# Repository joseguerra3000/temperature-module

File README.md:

Temperature Module
==================
Temperature module of small dimensions (approximately 45x25mm), compatible with arduino and digilent cerebot.
Useful for data acquisition systems based on microcontrollers (arduino, pic, etc.) and as a thermoresistor calibrator.
Able to use three temperature sensors at the same time:
  - LM35
  - AD22103
  - thermoresistor

How to use it
-------------
It only needs to be powered with +5V and +3.3V to measure temperatures greater thad 0°C with LM35 and AD22103 sensors. 
Optionally it can also be supplied with -5V to measure temperatures below 0°C with the LM35 sensor.
J3 is used as power switch for thermo-resistor, this allows it to be used with systems which reference is +5V or +3.3V
It offers three independent analog outputs, one for each sensor.

In addition, a library is included for use with arduino.

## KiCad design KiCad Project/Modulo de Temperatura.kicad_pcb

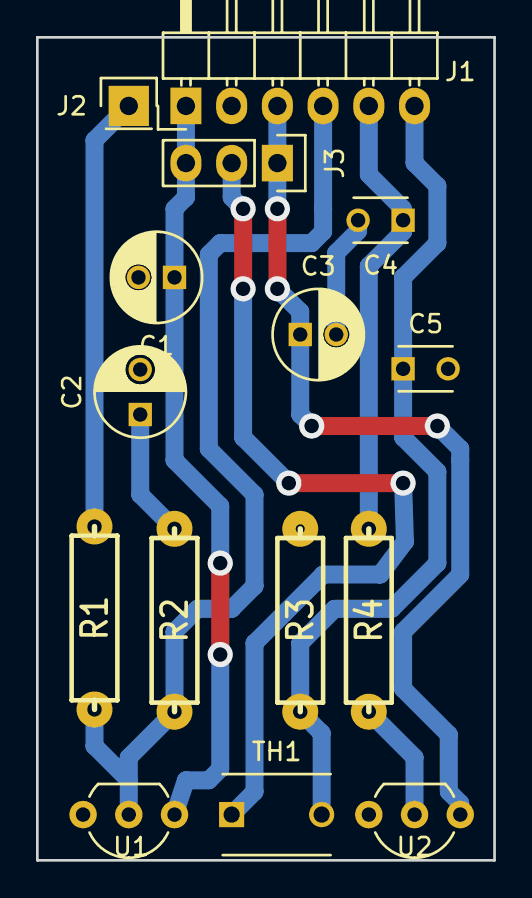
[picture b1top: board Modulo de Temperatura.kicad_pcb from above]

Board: 2 copper layers, 25.4 x 45.7 mm, 15 parts (0 on the bottom side), 10 nets.

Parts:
C1, C3: 0.1uF; C_Radial_D5_L11_P2
C2: 1uF; C_Radial_D5_L11_P2.5
C4, C5: 100nF; C_Disc_D3_P2.5
J1: HEADER_6; Pin_Header_Angled_1x06
J2: HEADER_1; Pin_Header_Straight_1x01
J3: HEADER_3; Pin_Header_Straight_1x03
R1: 100k; RC05
R2: 75; RC05
R3: 10k; RC05
R4: 1k; RC05
TH1: 20k; C_Disc_D6_P5
U1: LM35CZ; TO-92_Inline_Wide
U2: AD22103KT; TO-92_Inline_Wide

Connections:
+3V3: C3.1, J1.3, J3.1, U2.1
+5V: C1.1, J1.1, J3.3, U1.1
-5V: J2.1, R1.2
AD22103K_Output: C4.1, J1.5, R4.1
Earth: C1.2, C2.2, C3.2, C4.2, C5.2, J1.2, R3.2, U1.3, U2.3
LM35_Output: J1.4, R1.1, R2.1, U1.2
unnamed: C2.1, R2.2
unnamed: J3.2, TH1.1
unnamed: R4.2, U2.2
THERMISTOR_Output: C5.1, J1.6, R3.1, TH1.2

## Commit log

2018-01-09 README modified
